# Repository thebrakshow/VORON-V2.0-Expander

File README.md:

# VORON-V2.0-Expander
Expansion PCB to add 3 additional stepper drivers and 2 external PWM fans to a standard RAMPS 1.4 shield

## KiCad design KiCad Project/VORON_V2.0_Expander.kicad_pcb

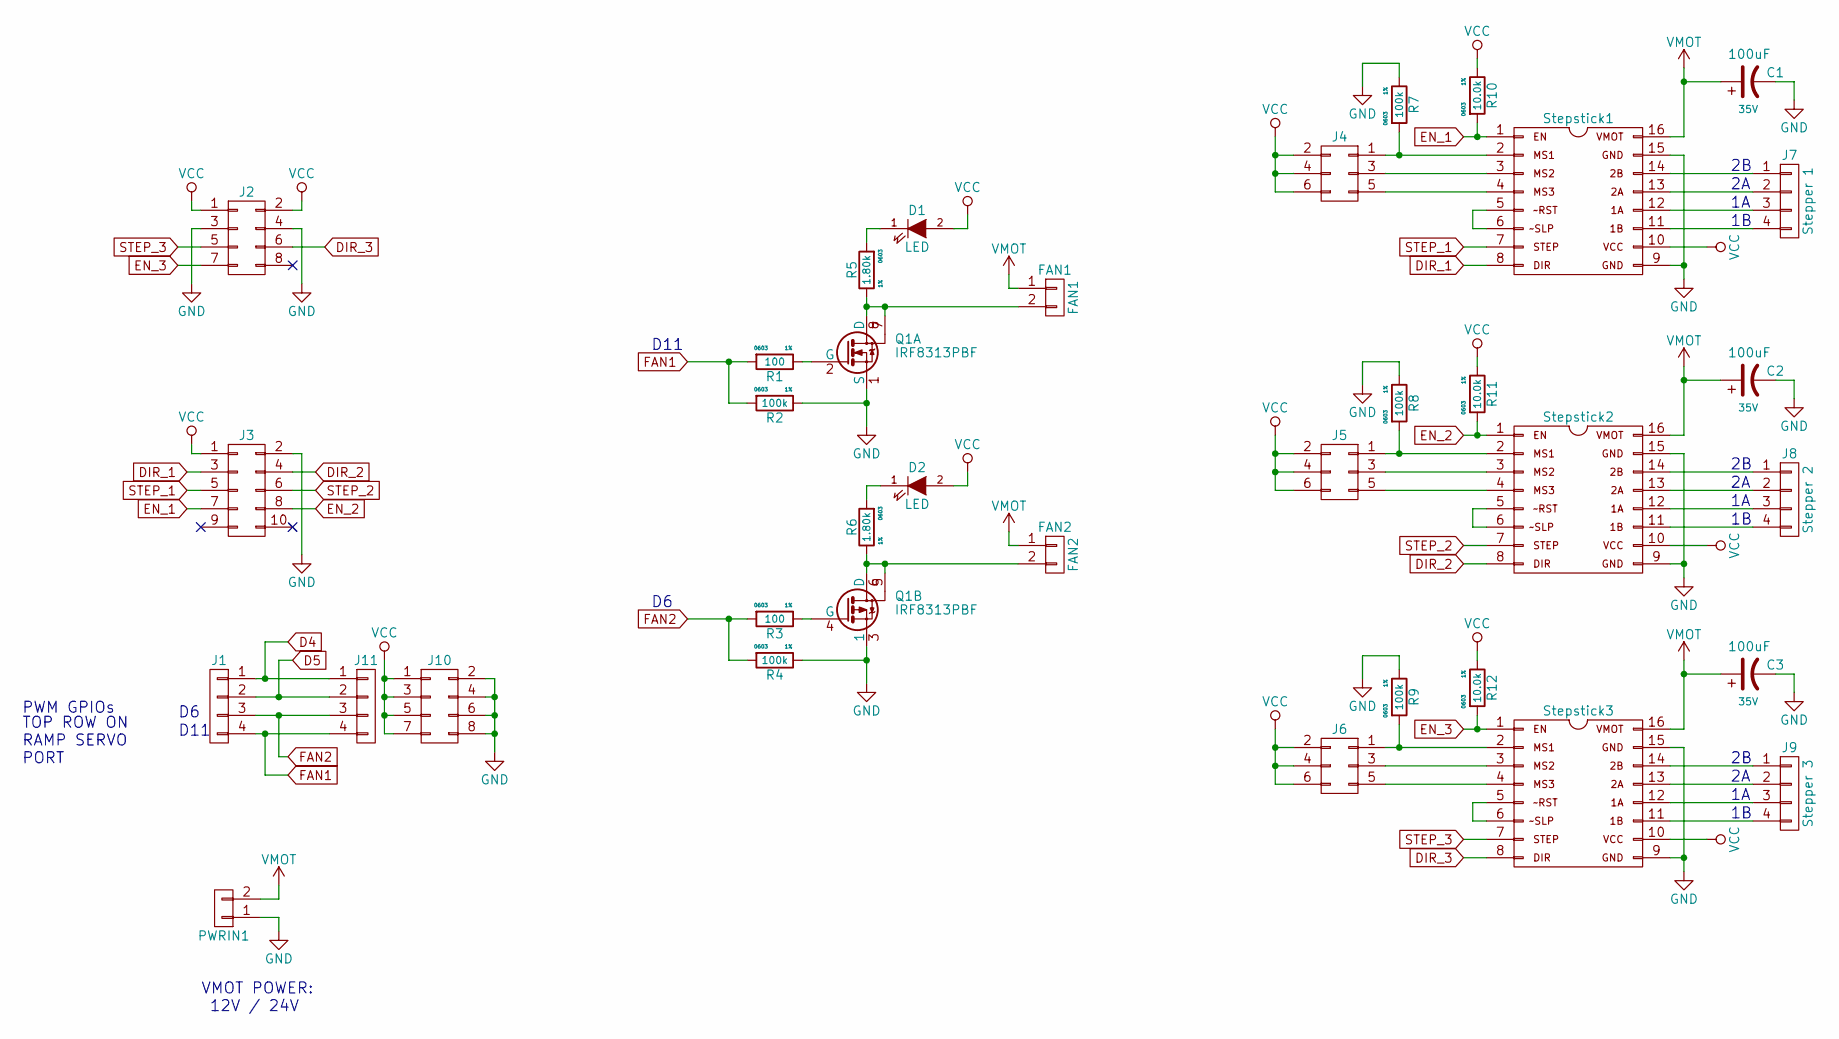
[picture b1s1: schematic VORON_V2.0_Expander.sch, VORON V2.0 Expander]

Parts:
C1, C2, C3: 100uF; c_elec_6.3x7.7; Voltage 35V
D1, D2: LED; LED_0805
FAN1: FAN1; 1X2_PIN_HEADER
FAN2: FAN2; 1X2_PIN_HEADER
J1, J11: 1X04_PIN_SOCKET
J2, J10: CONN_02X04; 2X4_PIN_SOCKET
J3: CONN_02X05; 2X5_PIN_SOCKET
J4, J5, J6: CONN_02X03; 2X03_PIN_HEADER
J7: Stepper 1; 1X04_PIN_HEADER
J8: Stepper 2; 1X04_PIN_HEADER
J9: Stepper 3; 1X04_PIN_HEADER
PWRIN1: PWRIN; mkds_1,5-2
Q1: IRF8313PBF; SOIC-8_3.9x4.9mm_Pitch1.27mm
R1, R3: 100; R_0603; Tolerance 1%
R2, R4, R7, R8, R9: 100k; R_0603; Tolerance 1%
R5, R6: 1.80k; R_0603; Tolerance 1%
R10, R11, R12: 10.0k; R_0603; Tolerance 1%
Stepstick1, Stepstick2, Stepstick3: Stepstick

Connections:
D4: J1.1, J11.1
D5: J1.2, J11.2
DIR_1: J3.3, Stepstick1.8; also elsewhere on the board
DIR_2: J3.4, Stepstick2.8; also elsewhere on the board
DIR_3: J2.6, Stepstick3.8; also elsewhere on the board
EN_1: J3.7, R10.2, Stepstick1.1; also elsewhere on the board
EN_2: J3.8, R11.2, Stepstick2.1; also elsewhere on the board
EN_3: J2.7, R12.2, Stepstick3.1; also elsewhere on the board
FAN1: J1.4, J11.4, R1.2, R2.2
FAN2: J1.3, J11.3, R3.2, R4.2
GND: C1.2, C2.2, C3.2, J2.3, J2.4, J3.2, J10.2, J10.4, J10.6, J10.8, PWRIN1.1, Q1.1 (S), Q1.3 (1), R2.1, R4.1, R7.1, R8.1, R9.1, Stepstick1.9, Stepstick1.15, Stepstick2.9, Stepstick2.15, Stepstick3.9, Stepstick3.15; also elsewhere on the board
unnamed: D1.1 (K), R5.2
unnamed: D2.1 (K), R6.2
unnamed: FAN1.2, Q1.7, Q1.8 (D), R5.1
unnamed: FAN2.2, Q1.5, Q1.6 (D), R6.1
unnamed 18: J4.1, R7.2, Stepstick1.2; also elsewhere on the board
unnamed 19: J4.3, Stepstick1.3; also elsewhere on the board
unnamed 20: J4.5, Stepstick1.4; also elsewhere on the board
unnamed 21: J5.1, R8.2, Stepstick2.2; also elsewhere on the board
unnamed 22: J5.3, Stepstick2.3; also elsewhere on the board
unnamed 23: J5.5, Stepstick2.4; also elsewhere on the board
unnamed 24: J6.1, R9.2, Stepstick3.2; also elsewhere on the board
unnamed 25: J6.3, Stepstick3.3; also elsewhere on the board
unnamed 26: J6.5, Stepstick3.4; also elsewhere on the board
unnamed 27: J7.1, Stepstick1.14; also elsewhere on the board
unnamed 28: J7.2, Stepstick1.13; also elsewhere on the board
unnamed 29: J7.3, Stepstick1.12; also elsewhere on the board
unnamed 30: J7.4, Stepstick1.11; also elsewhere on the board
unnamed 31: J8.1, Stepstick2.14; also elsewhere on the board
unnamed 32: J8.2, Stepstick2.13; also elsewhere on the board
unnamed 33: J8.3, Stepstick2.12; also elsewhere on the board
unnamed 34: J8.4, Stepstick2.11; also elsewhere on the board
unnamed 35: J9.1, Stepstick3.14; also elsewhere on the board
unnamed 36: J9.2, Stepstick3.13; also elsewhere on the board
unnamed 37: J9.3, Stepstick3.12; also elsewhere on the board
unnamed 38: J9.4, Stepstick3.11; also elsewhere on the board
unnamed: Q1.2 (G), R1.1
unnamed: Q1.4 (G), R3.1
unnamed 41: Stepstick1.5, Stepstick1.6; also elsewhere on the board
unnamed 42: Stepstick2.5, Stepstick2.6; also elsewhere on the board
unnamed 43: Stepstick3.5, Stepstick3.6; also elsewhere on the board
STEP_1: J3.5, Stepstick1.7; also elsewhere on the board
STEP_2: J3.6, Stepstick2.7; also elsewhere on the board
STEP_3: J2.5, Stepstick3.7; also elsewhere on the board
VCC: D1.2 (A), D2.2 (A), J2.1, J2.2, J3.1, J4.2, J4.4, J4.6, J5.2, J5.4, J5.6, J6.2, J6.4, J6.6, J10.1, J10.3, J10.5, J10.7, R10.1, R11.1, R12.1, Stepstick1.10, Stepstick2.10, Stepstick3.10; also elsewhere on the board
VMOT: C1.1, C2.1, C3.1, FAN1.1, FAN2.1, PWRIN1.2, Stepstick1.16, Stepstick2.16, Stepstick3.16; also elsewhere on the board

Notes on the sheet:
D11
PWM GPIOs
TOP ROW ON RAMP SERVO PORT
VMOT POWER: 12V / 24V

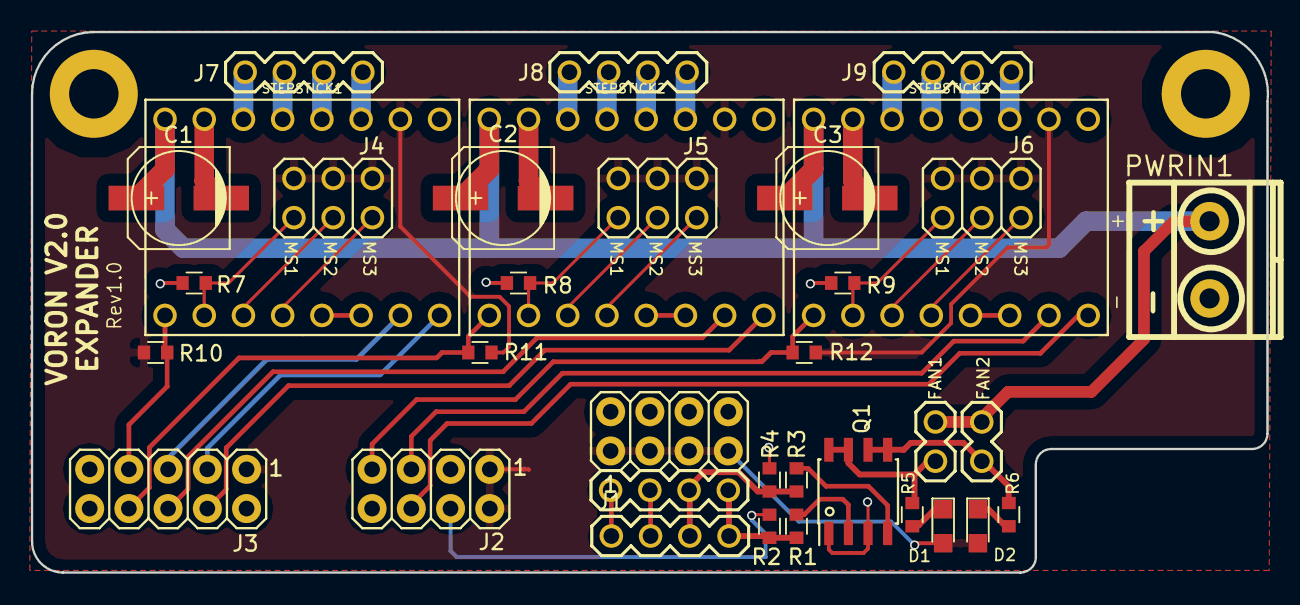
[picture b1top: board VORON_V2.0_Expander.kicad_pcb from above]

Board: 2 copper layers, 80.0 x 35.0 mm, 35 parts (0 on the bottom side), 46 nets.

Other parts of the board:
STEPSTICK1, STEPSTICK2, STEPSTICK3: Stepstick

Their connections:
DIR_1: STEPSTICK1.8; also elsewhere on the board
DIR_2: STEPSTICK2.8; also elsewhere on the board
DIR_3: STEPSTICK3.8; also elsewhere on the board
EN_1: STEPSTICK1.1; also elsewhere on the board
EN_2: STEPSTICK2.1; also elsewhere on the board
EN_3: STEPSTICK3.1; also elsewhere on the board
GND: STEPSTICK1.9, STEPSTICK1.15, STEPSTICK2.9, STEPSTICK2.15, STEPSTICK3.9, STEPSTICK3.15; also elsewhere on the board
unnamed 18: STEPSTICK1.2; also elsewhere on the board
unnamed 19: STEPSTICK1.3; also elsewhere on the board
unnamed 20: STEPSTICK1.4; also elsewhere on the board
unnamed 21: STEPSTICK2.2; also elsewhere on the board
unnamed 22: STEPSTICK2.3; also elsewhere on the board
unnamed 23: STEPSTICK2.4; also elsewhere on the board
unnamed 24: STEPSTICK3.2; also elsewhere on the board
unnamed 25: STEPSTICK3.3; also elsewhere on the board
unnamed 26: STEPSTICK3.4; also elsewhere on the board
unnamed 27: STEPSTICK1.14; also elsewhere on the board
unnamed 28: STEPSTICK1.13; also elsewhere on the board
unnamed 29: STEPSTICK1.12; also elsewhere on the board
unnamed 30: STEPSTICK1.11; also elsewhere on the board
unnamed 31: STEPSTICK2.14; also elsewhere on the board
unnamed 32: STEPSTICK2.13; also elsewhere on the board
unnamed 33: STEPSTICK2.12; also elsewhere on the board
unnamed 34: STEPSTICK2.11; also elsewhere on the board
unnamed 35: STEPSTICK3.14; also elsewhere on the board
unnamed 36: STEPSTICK3.13; also elsewhere on the board
unnamed 37: STEPSTICK3.12; also elsewhere on the board
unnamed 38: STEPSTICK3.11; also elsewhere on the board
unnamed 41: STEPSTICK1.5, STEPSTICK1.6; also elsewhere on the board
unnamed 42: STEPSTICK2.5, STEPSTICK2.6; also elsewhere on the board
unnamed 43: STEPSTICK3.5, STEPSTICK3.6; also elsewhere on the board
STEP_1: STEPSTICK1.7; also elsewhere on the board
STEP_2: STEPSTICK2.7; also elsewhere on the board
STEP_3: STEPSTICK3.7; also elsewhere on the board
VCC: STEPSTICK1.10, STEPSTICK2.10, STEPSTICK3.10; also elsewhere on the board
VMOT: STEPSTICK1.16, STEPSTICK2.16, STEPSTICK3.16; also elsewhere on the board

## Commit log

2017-10-16 Create read
2017-10-16 Create read
2017-10-16 Add files via upload
    VORON V2.0 Expander Schematic
2017-10-16 Create TODO
2017-10-16 Update TODO
2017-10-16 Create Pictures
2017-10-16 Create test
